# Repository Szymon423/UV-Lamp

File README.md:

<div align="center">

# 💅 UV Lamp Project

*A custom-made UV lamp for nail polish curing*

</div>

---

## 📖 About

In this project, I wanted to address a common issue in the beauty industry: **misleading UV lamp specifications**. 

Most commercial UV lamps are advertised as "60W UV lamps" while being supplied with only 15W power adapters. I wanted to create something honest and effective, so I designed this lamp from scratch.

### ✨ Key Features

- **True 45W electrical power** - honest specifications
- **Adjustable power settings** - customize intensity from 0-100%
- **Configurable timer** - set precise curing times up to 3 minutes
- **Intuitive touchscreen interface** - easy configuration with rotary encoder
- **Settings persistence** - preferences saved in flash memory
- **Professional UV wavelength** - 395-405nm LEDs for optimal curing

<div align="center">

### 🎨 Main Design

### 🖼️ Detailed Views

<table>
  <tr>
    <td width="50%">
      
    </td>
    <td width="50%">
      
    </td>
  </tr>
  <tr>
    <td width="50%">
      
    </td>
    <td width="50%">
      
    </td>
  </tr>
  <tr>
    <td width="50%">
      
    </td>
    <td width="50%">
      
    </td>
  </tr>
  <tr>
    <td width="50%">
      
    </td>
    <td cwidth="50%">
      
    </td>
  </tr>
</table>

</div>

---

## ⚡ Hardware Design

The hardware was designed in **KiCad** around the **Raspberry Pi RP2040** microcontroller. The lamp is powered through a C8 socket connector from 230V AC mains.

### 🔧 PCB Architecture

The system consists of three types of PCBs:

1. **Power & Driver Board**
   - Converts 230V AC to 48V DC for LED drivers
   - Provides 3.3V DC for microcontroller and peripherals
   - LED current drivers with PWM control capability

2. **Control Board**
   - RP2040 microcontroller
   - 1.69" LCD display with LVGL interface
   - Rotary encoder for navigation
   - Two control buttons
   - Flash memory for settings storage

3. **LED Arrays**
   - Multiple LED strings with 395-405nm wavelength
   - Optimized thermal management
   - Uniform light distribution

### 📊 Technical Specifications

- **Input voltage:** 230V AC (50/60Hz)
- **LED power:** 48V DC, up to 45W total
- **UV wavelength:** 395-405nm
- **Control:** PWM dimming, 0-100%
- **Timer range:** 0-180 seconds
- **Display:** 1.69" color LCD (280x240)

---

## 💻 Software

The firmware is written in C for the RP2040 and utilizes the following technologies:

### 🛠️ Core Technologies

- **LVGL (Light and Versatile Graphics Library)** - for the graphical interface
- **SquareLine Studio** - for UI design
- **Pico SDK** - official Raspberry Pi development kit
- **Hardware PWM** - for precise LED dimming control

### 🖥️ User Interface

<div align="center">

</div>

The interface features three main screens:

1. **Main Screen** - displays current timer and power settings with arc progress indicator
2. **Power Configuration** - adjust UV intensity from 0-100%
3. **Timer Configuration** - set curing time from 0 to 180 seconds

### 🎮 Controls

- **Rotary Encoder** - navigate and adjust values
- **Button 1** - short press: change screen | long press: enter/exit edit mode
- **Button 2** - short press: start/pause timer | long press: reset timer

### 🚀 Features

- Smooth animations and transitions
- Real-time countdown with arc visualization
- Automatic settings save to flash memory
- Debounced button inputs with long-press detection
- 30 FPS refresh rate for fluid UI

---

## 📜 License

This project is open source. Feel free to use, modify, and distribute according to the license terms.

---

## 🙏 Acknowledgments

This project was created because my girlfriend complained about her unreliable UV lamp. It combines my passion for electronics and design with practical problem-solving.

---

<div align="center">

*Made with dedication to quality and honesty*

</div>

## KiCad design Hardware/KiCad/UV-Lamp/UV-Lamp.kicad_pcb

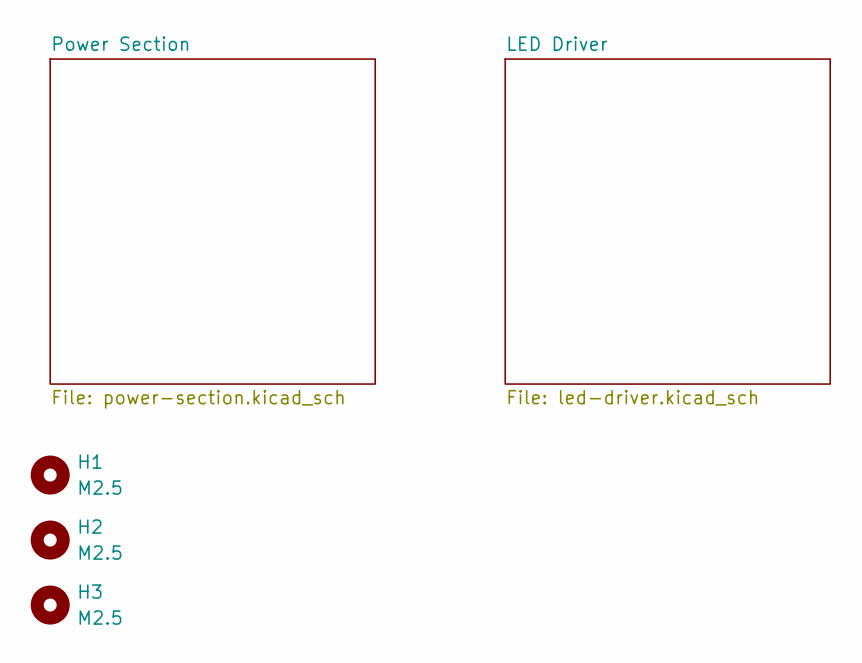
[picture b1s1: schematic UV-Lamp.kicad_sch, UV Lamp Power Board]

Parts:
H1, H2, H3: M2.5; MountingHole_2.7mm_M2.5

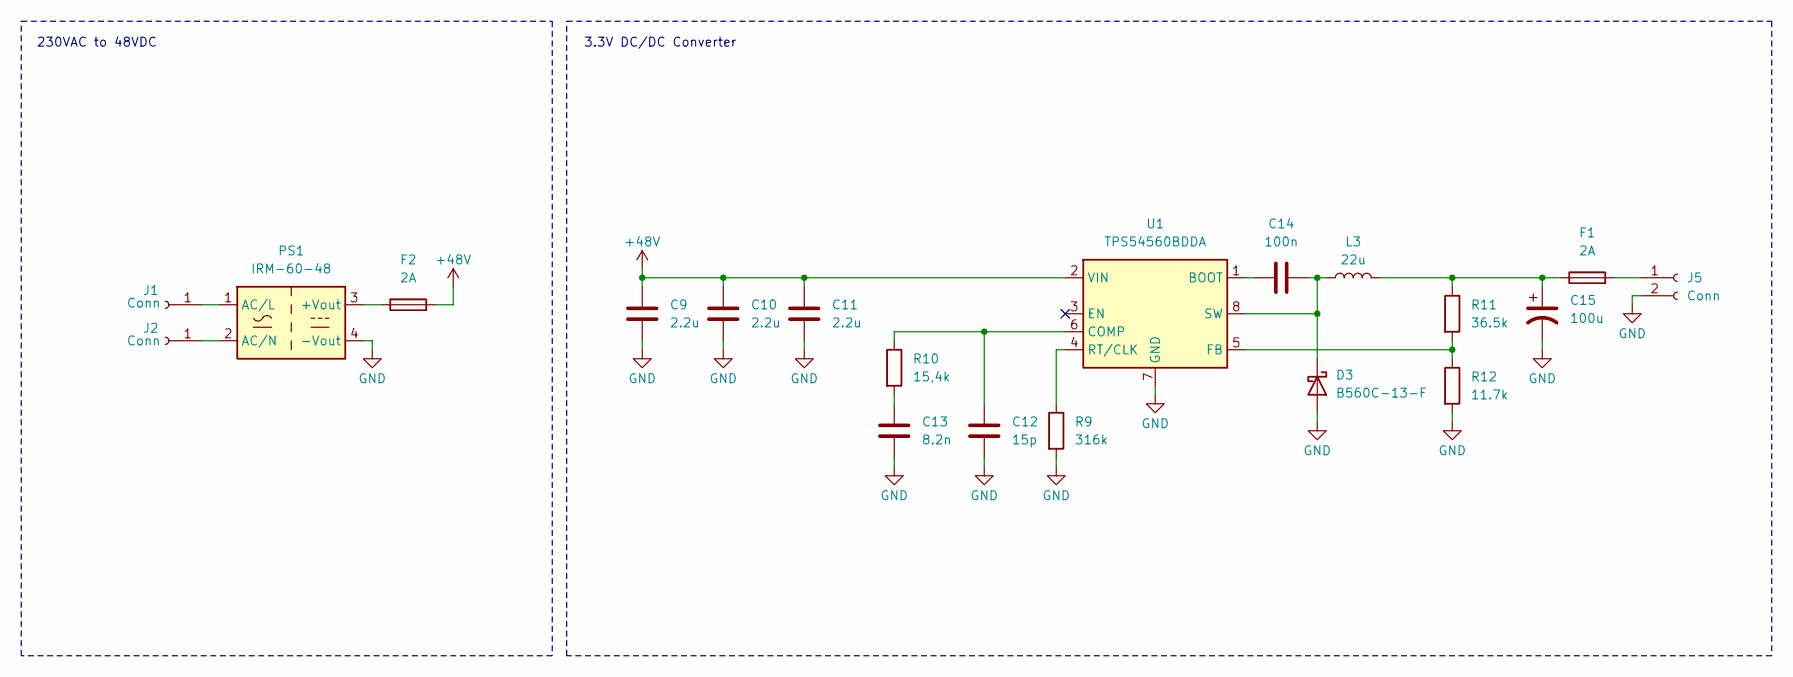
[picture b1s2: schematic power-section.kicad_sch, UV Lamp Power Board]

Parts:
C9, C10, C11: 2.2u; C_1206_3216Metric
C12: 15p; C_0805_2012Metric
C13: 8.2n; C_0805_2012Metric
C14: 100n; C_0805_2012Metric
C15: 100u; CP_Elec_6.3x7.7
D3: B560C-13-F; D_SMC
F1, F2: 2A; Fuse_1206_3216Metric
J1, J2: Conn; SolderWire-1.5sqmm_1x01_D1.7mm_OD3.9mm
J5: Conn; SolderWire-1sqmm_1x02_P5.4mm_D1.4mm_OD2.7mm
L3: 22u; L_12x12mm_H6mm
PS1: IRM-60-48; Converter_ACDC_MeanWell_IRM-60-xx_THT
R9: 316k; R_0805_2012Metric
R10: 15,4k; R_0805_2012Metric
R11: 36.5k; R_0805_2012Metric
R12: 11.7k; R_0805_2012Metric
U1: TPS54560BDDA; Texas_R-PDSO-G8_EP2.95x4.9mm_Mask2.4x3.1mm_ThermalVias

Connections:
+48V: C9.1, C10.1, C11.1, F2.2, U1.2 (VIN); also elsewhere on the board
GND: C9.2, C10.2, C11.2, C12.2, C13.2, C15.2, D3.2 (A), J5.2, PS1.4 (-Vout), R9.2, R12.2, U1.7 (GND), U1.9 (GND); also elsewhere on the board
unnamed: C13.1, R10.2
unnamed: C15.1, F1.1, L3.2, R11.1
unnamed: C14.2, D3.1 (K), L3.1, U1.8 (SW)
unnamed: J1.1, PS1.1 (AC/L)
unnamed: J2.1, PS1.2 (AC/N)
unnamed: F1.2, J5.1
unnamed: F2.1, PS1.3 (+Vout)
unnamed: C14.1, U1.1 (BOOT)
unnamed: C12.1, R10.1, U1.6 (COMP)
unnamed: R11.2, R12.1, U1.5 (FB)
unnamed: R9.1, U1.4 (RT/CLK)

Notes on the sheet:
230VAC to 48VDC
3.3V DC/DC Converter

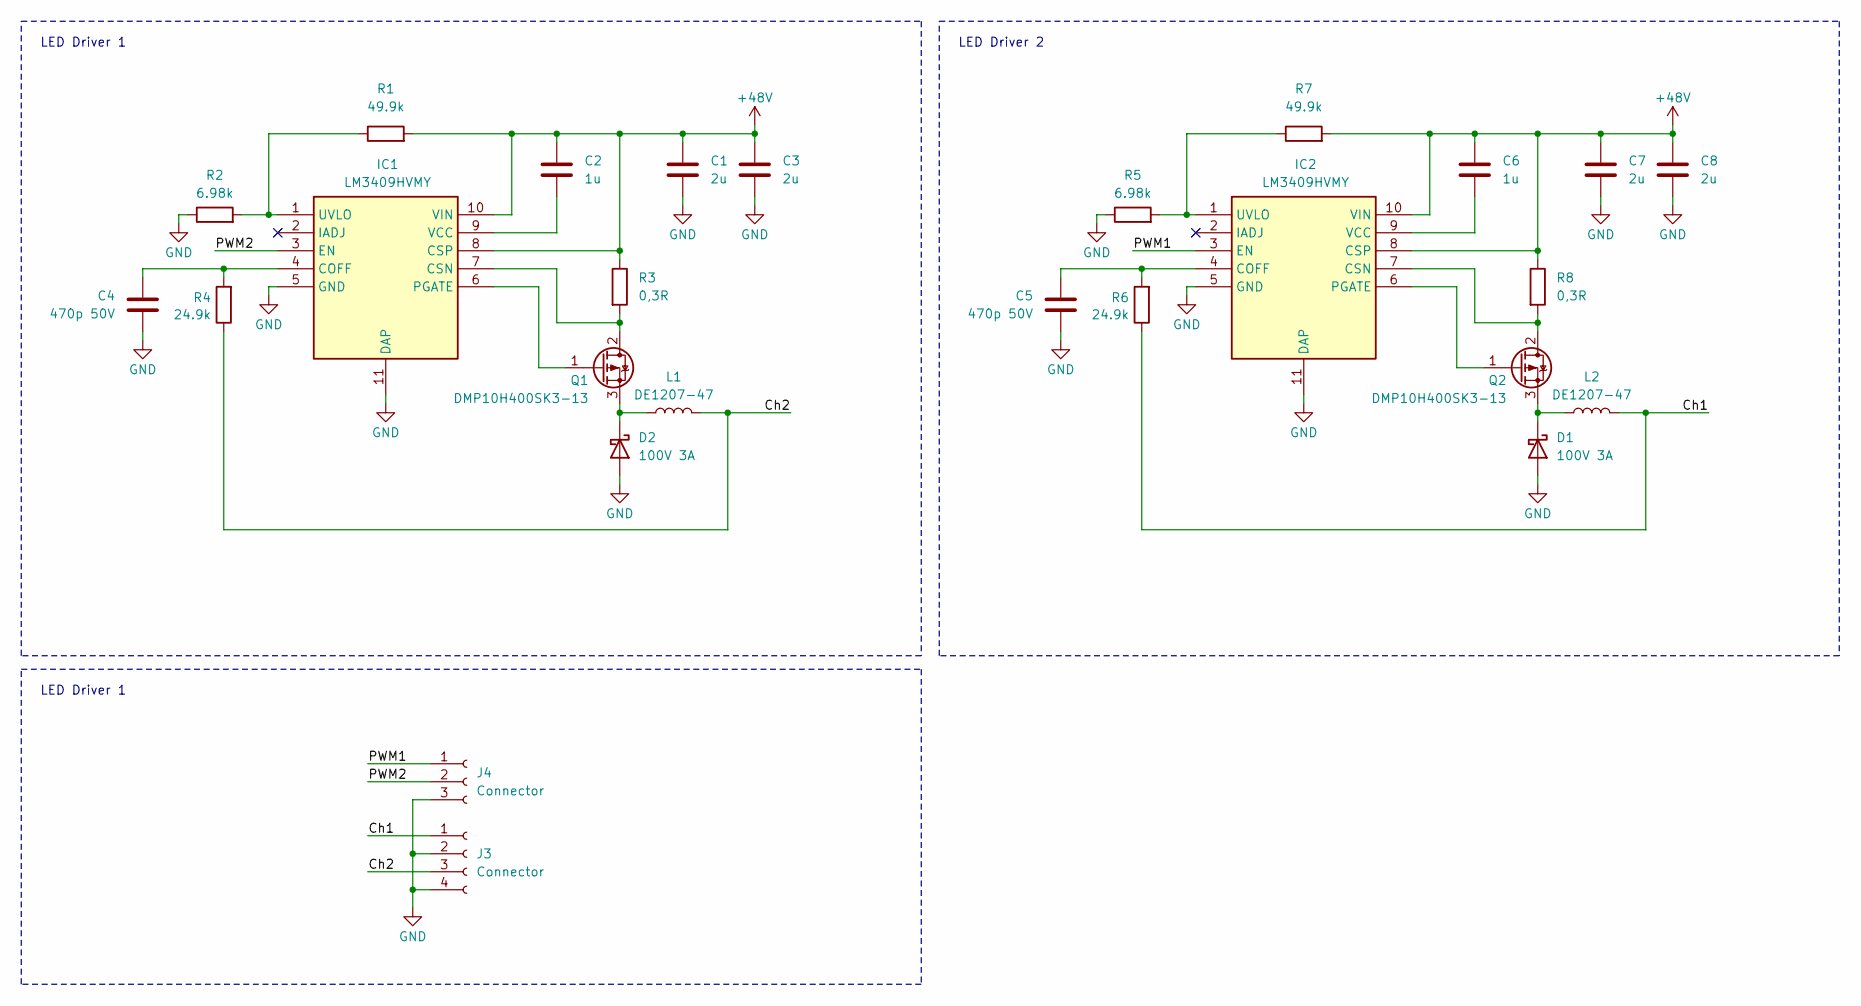
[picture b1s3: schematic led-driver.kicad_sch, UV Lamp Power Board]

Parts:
C1, C3, C7, C8: 2u; C_1206_3216Metric
C2, C6: 1u; C_0805_2012Metric
C4, C5: 470p 50V; C_0805_2012Metric
D1, D2: 100V 3A; D_SMC
IC1, IC2: LM3409HVMY; Manufacturer_Part_Number LM3409HVMY/NOPB
J3: Connector; SolderWire-1.5sqmm_1x04_P6mm_D1.7mm_OD3mm
J4: Connector; SolderWire-0.5sqmm_1x03_P4.6mm_D0.9mm_OD2.1mm
L1, L2: DE1207-47; L_12x12mm_H6mm
Q1, Q2: DMP10H400SK3-13; TO-252-2
R1, R7: 49.9k; R_0805_2012Metric
R2, R5: 6.98k; R_0805_2012Metric
R3, R8: 0,3R; R_2512_6332Metric
R4, R6: 24.9k; R_0805_2012Metric

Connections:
+48V: C1.1, C2.1, C3.1, C6.1, C7.1, C8.1, IC1.8 (CSP), IC1.10 (VIN), IC2.8 (CSP), IC2.10 (VIN), R1.2, R3.1, R7.2, R8.1; also elsewhere on the board
/LED Driver/Ch1: J3.1, L2.2, R6.1
/LED Driver/Ch2: J3.3, L1.2, R4.1
/LED Driver/PWM1: IC2.3 (EN), J4.1
/LED Driver/PWM2: IC1.3 (EN), J4.2
GND: C1.2, C3.2, C4.2, C5.2, C7.2, C8.2, D1.2 (A), D2.2 (A), IC1.5 (GND), IC1.11 (DAP), IC2.5 (GND), IC2.11 (DAP), J3.2, J3.4, J4.3, R2.1, R5.1; also elsewhere on the board
unnamed: D1.1 (K), L2.1, Q2.3 (S)
unnamed: D2.1 (K), L1.1, Q1.3 (S)
unnamed: C4.1, IC1.4 (COFF), R4.2
unnamed: IC1.7 (CSN), Q1.2 (D), R3.2
unnamed: IC1.6 (PGATE), Q1.1 (G)
unnamed: IC1.1 (UVLO), R1.1, R2.2
unnamed: C2.2, IC1.9 (VCC)
unnamed: C5.1, IC2.4 (COFF), R6.2
unnamed: IC2.7 (CSN), Q2.2 (D), R8.2
unnamed: IC2.6 (PGATE), Q2.1 (G)
unnamed: IC2.1 (UVLO), R5.2, R7.1
unnamed: C6.2, IC2.9 (VCC)

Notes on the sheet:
LED Driver 2
LED Driver 1

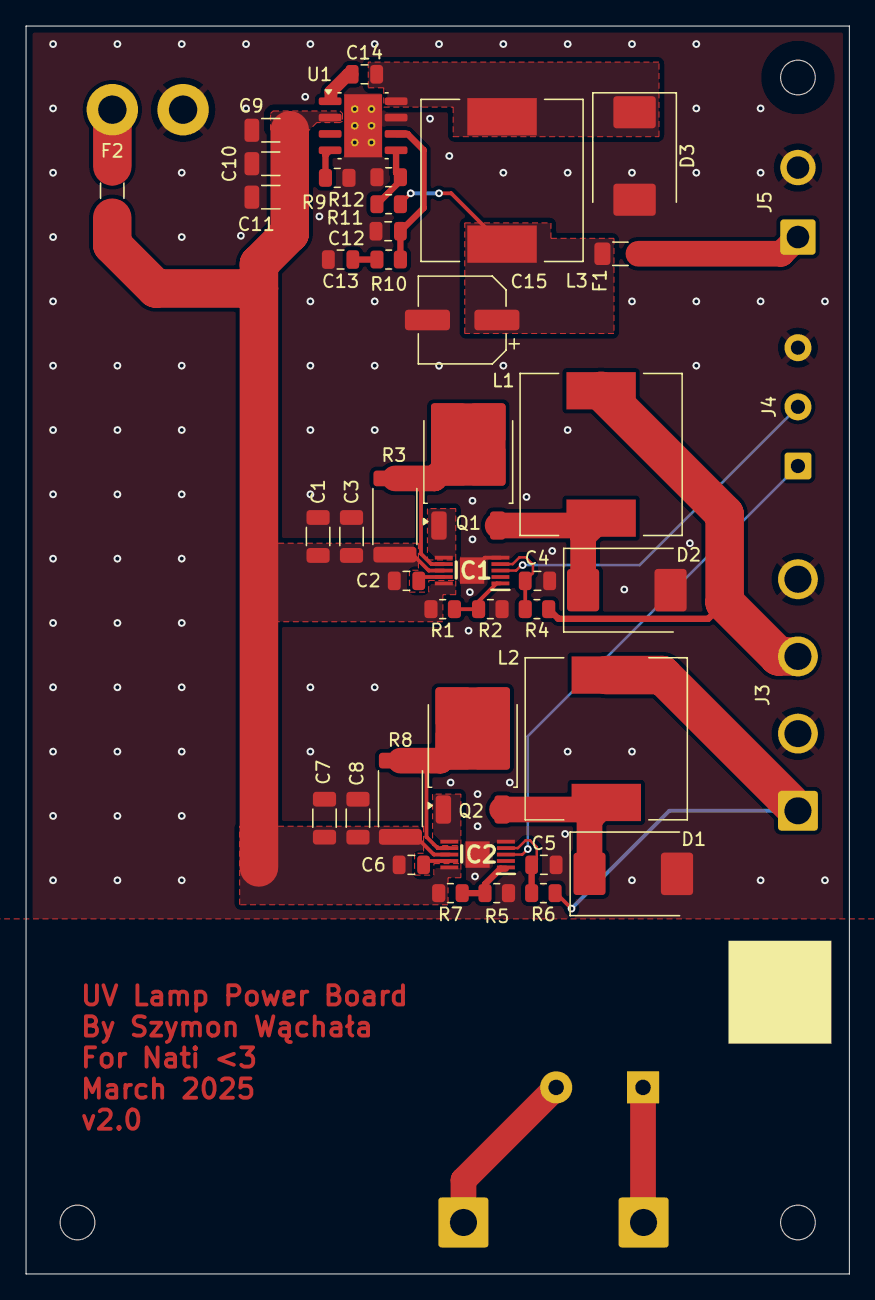
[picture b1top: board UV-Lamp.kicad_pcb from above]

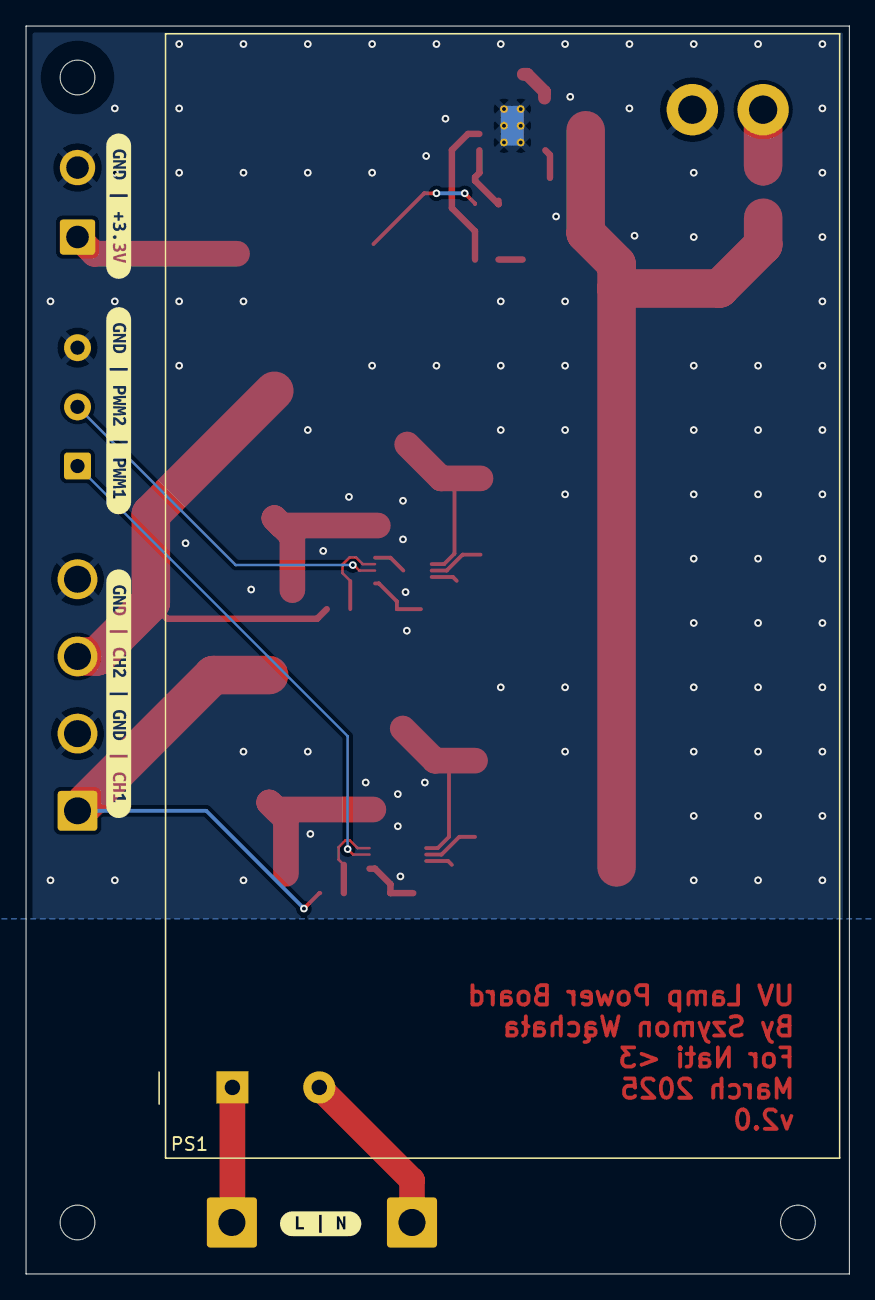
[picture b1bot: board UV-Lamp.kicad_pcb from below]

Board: 2 copper layers, 64.0 x 97.0 mm, 53 parts (5 on the bottom side), 29 nets.

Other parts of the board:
kibuzzard-67E995BA: G***; kibuzzard-67E995BA
kibuzzard-67E9956E: G***; kibuzzard-67E9956E
kibuzzard-67E99536: G***; kibuzzard-67E99536
kibuzzard-67E99669: G***; kibuzzard-67E99669

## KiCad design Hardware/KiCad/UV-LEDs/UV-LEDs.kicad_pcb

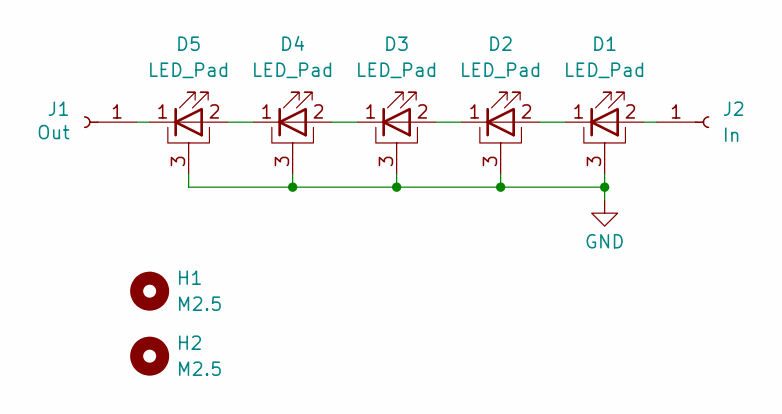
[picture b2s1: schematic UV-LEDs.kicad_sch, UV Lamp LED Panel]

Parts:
D1, D2, D3, D4, D5: LED_Pad; LED_Cree-XHP35
H1, H2: M2.5; MountingHole_2.7mm_M2.5
J1: Out; SolderWire-1.5sqmm_1x01_D1.7mm_OD3.9mm
J2: In; SolderWire-1.5sqmm_1x01_D1.7mm_OD3.9mm

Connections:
GND: D1.3 (PAD), D2.3 (PAD), D3.3 (PAD), D4.3 (PAD), D5.3 (PAD)
unnamed: D1.2 (A), J2.1
unnamed: D1.1 (K), D2.2 (A)
unnamed: D2.1 (K), D3.2 (A)
unnamed: D3.1 (K), D4.2 (A)
unnamed: D4.1 (K), D5.2 (A)
unnamed: D5.1 (K), J1.1

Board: 2 copper layers, 11 parts (0 on the bottom side), 7 nets, no tracks yet.

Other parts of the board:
kibuzzard-67E9A14C: G***; kibuzzard-67E9A14C
kibuzzard-67E9A164: G***; kibuzzard-67E9A164

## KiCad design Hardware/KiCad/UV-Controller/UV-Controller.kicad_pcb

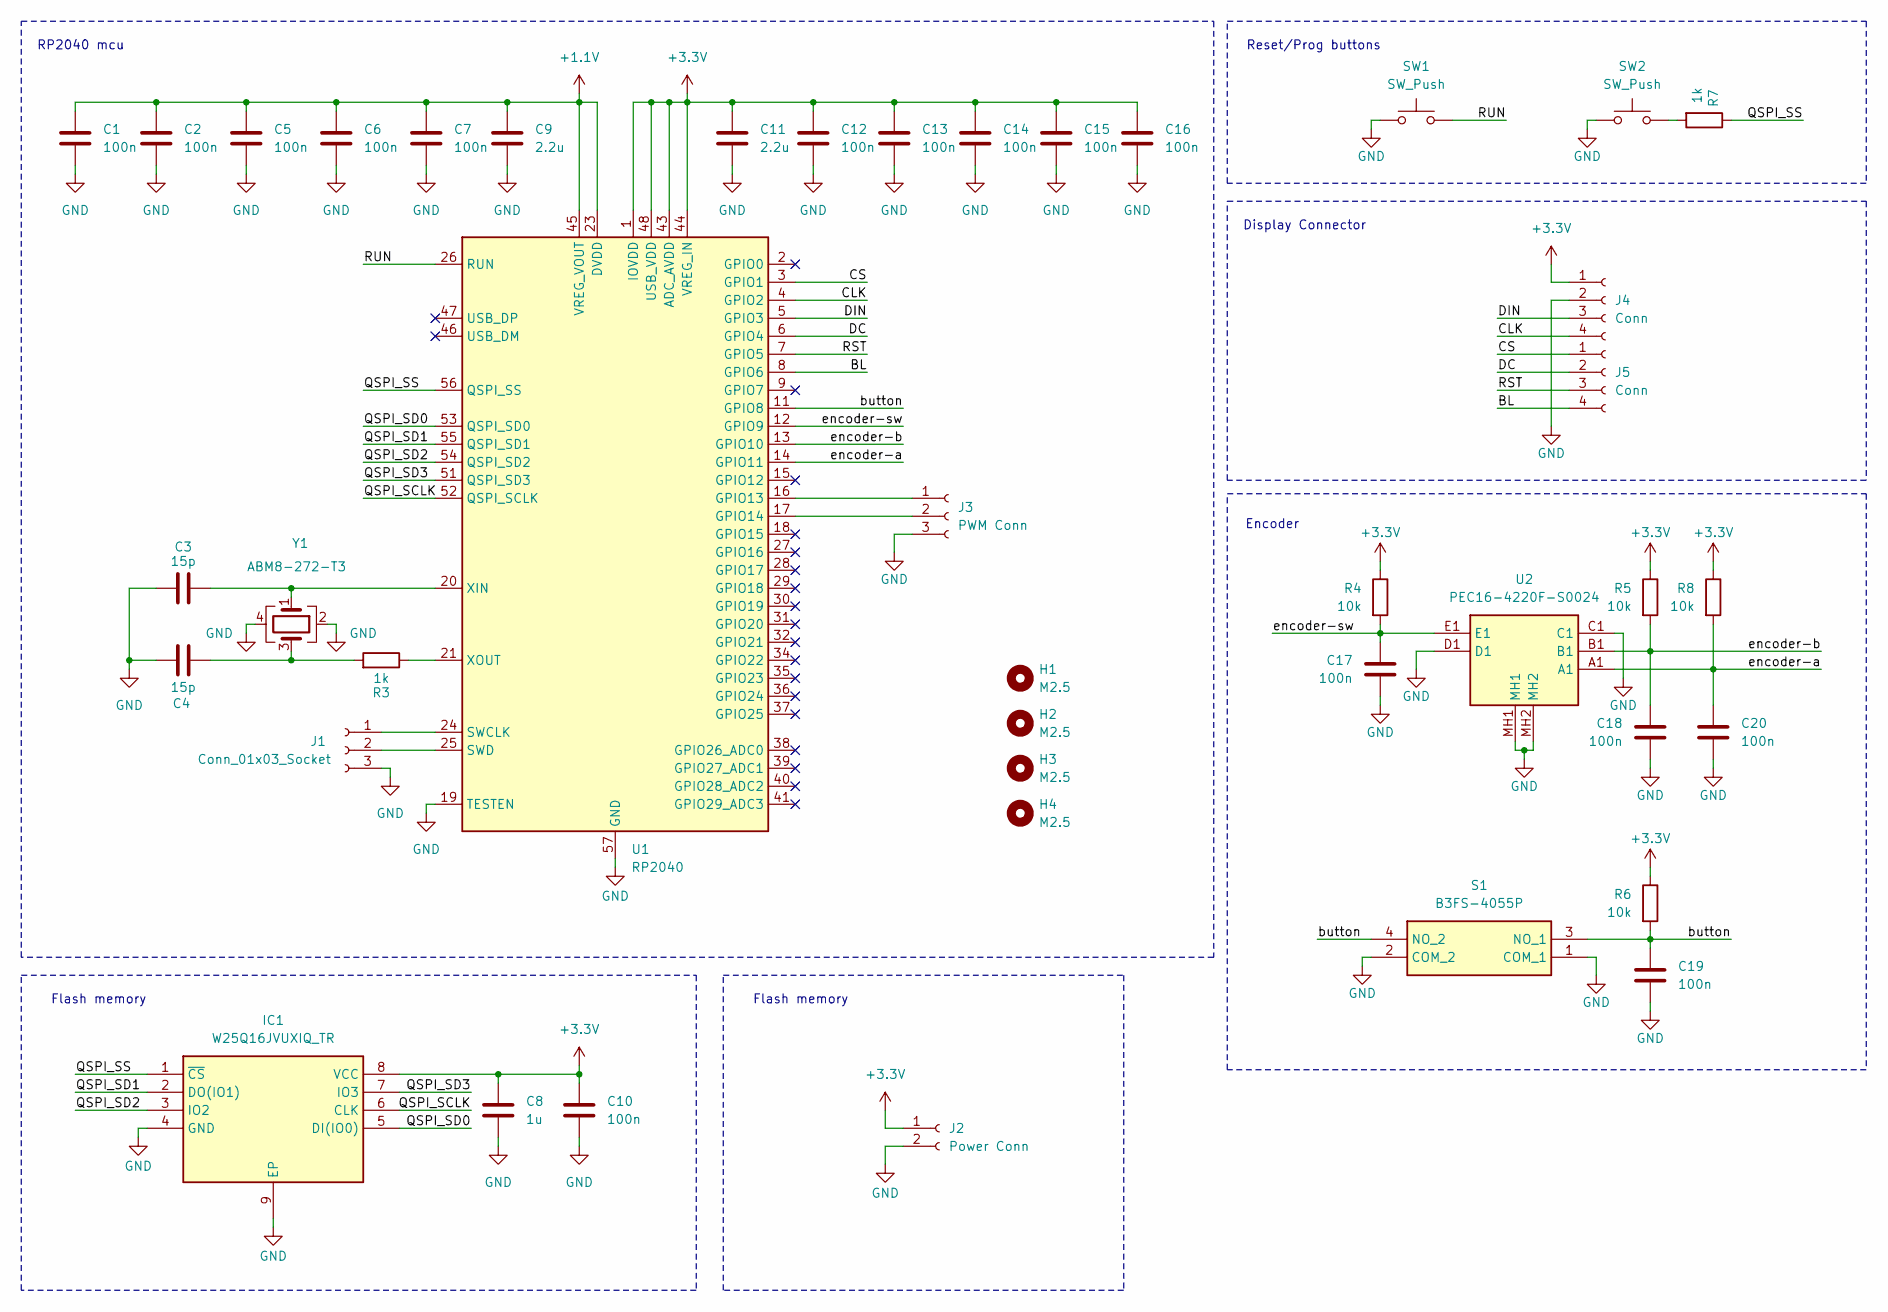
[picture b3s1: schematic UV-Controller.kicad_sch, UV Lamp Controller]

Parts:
C1, C2, C5, C6, C7, C10, C12, C13, C14, C15, C16: 100n; C_0402_1005Metric
C3, C4: 15p; C_0402_1005Metric
C8: 1u; C_0805_2012Metric
C9, C11: 2.2u; C_0805_2012Metric
C17, C18, C19, C20: 100n; C_0805_2012Metric
H1, H2, H3, H4: M2.5; MountingHole_2.7mm_M2.5
IC1: W25Q16JVUXIQ_TR; SON50P300X200X60-9N; Manufacturer_Part_Number W25Q16JVUXIQ TR
J1: Conn_01x03_Socket; JST_PH_S3B-PH-K_1x03_P2.00mm_Horizontal
J2: Power Conn; SolderWire-1.5sqmm_1x02_P6mm_D1.7mm_OD3mm
J3: PWM Conn; SolderWire-0.5sqmm_1x03_P4.6mm_D0.9mm_OD2.1mm
J4, J5: Conn; SolderWire-0.5sqmm_1x04_P4.6mm_D0.9mm_OD2.1mm
R3, R7: 1k; R_0402_1005Metric
R4, R5, R6, R8: 10k; R_0805_2012Metric
S1: B3FS-4055P; Manufacturer_Part_Number B3FS-4055P
SW1, SW2: SW_Push; SW_Tactile_SPST_NO_Straight_CK_PTS636Sx25SMTRLFS
U1: RP2040; QFN-56-1EP_7x7mm_P0.4mm_EP3.2x3.2mm_ThermalVias
U2: PEC16-4220F-S0024; Manufacturer_Part_Number PEC16-4220F-S0024
Y1: ABM8-272-T3; Crystal_SMD_Abracon_ABM3B-4Pin_5.0x3.2mm

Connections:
+1.1V: C1.1, C2.1, C5.1, C6.1, C7.1, C9.1, U1.23 (DVDD), U1.45 (VREG_VOUT), U1.50 (DVDD)
+3.3V: C8.1, C10.1, C11.1, C12.1, C13.1, C14.1, C15.1, C16.1, IC1.8 (VCC), J2.1, J4.1, R4.1, R5.1, R6.1, R8.1, U1.1 (IOVDD), U1.10 (IOVDD), U1.22 (IOVDD), U1.33 (IOVDD), U1.42 (IOVDD), U1.43 (ADC_AVDD), U1.44 (VREG_IN), U1.48 (USB_VDD), U1.49 (IOVDD)
/BL: J5.4, U1.8 (GPIO6)
/CLK: J4.4, U1.4 (GPIO2)
/CS: J5.1, U1.3 (GPIO1)
/DC: J5.2, U1.6 (GPIO4)
/DIN: J4.3, U1.5 (GPIO3)
/QSPI_SCLK: IC1.6 (CLK), U1.52 (QSPI_SCLK)
/QSPI_SD0: IC1.5 (DI(IO0)), U1.53 (QSPI_SD0)
/QSPI_SD1: IC1.2 (DO(IO1)), U1.55 (QSPI_SD1)
/QSPI_SD2: IC1.3 (IO2), U1.54 (QSPI_SD2)
/QSPI_SD3: IC1.7 (IO3), U1.51 (QSPI_SD3)
/QSPI_SS: IC1.1 (~CS), R7.1, U1.56 (QSPI_SS)
/RST: J5.3, U1.7 (GPIO5)
/RUN: SW1.2, U1.26 (RUN)
/button: C19.1, R6.2, S1.3 (NO_1), S1.4 (NO_2), U1.11 (GPIO8)
/encoder-a: C20.1, R8.2, U1.14 (GPIO11), U2.A1
/encoder-b: C18.1, R5.2, U1.13 (GPIO10), U2.B1
/encoder-sw: C17.1, R4.2, U1.12 (GPIO9), U2.E1
GND: C1.2, C2.2, C3.1, C4.1, C5.2, C6.2, C7.2, C8.2, C9.2, C10.2, C11.2, C12.2, C13.2, C14.2, C15.2, C16.2, C17.2, C18.2, C19.2, C20.2, IC1.4 (GND), IC1.9 (EP), J1.3, J2.2, J3.3, J4.2, S1.1 (COM_1), S1.2 (COM_2), SW1.1, SW2.1, U1.19 (TESTEN), U1.57 (GND), U2.C1, U2.D1, U2.MH1, U2.MH2, Y1.2, Y1.4
unnamed: C4.2, R3.2, Y1.3
unnamed: J1.1, U1.24 (SWCLK)
unnamed: J1.2, U1.25 (SWD)
unnamed: J3.1, U1.16 (GPIO13)
unnamed: J3.2, U1.17 (GPIO14)
unnamed: R7.2, SW2.2
unnamed: C3.2, U1.20 (XIN), Y1.1
unnamed: R3.1, U1.21 (XOUT)

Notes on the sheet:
Encoder
Display Connector
Flash memory
RP2040 mcu
Reset/Prog buttons

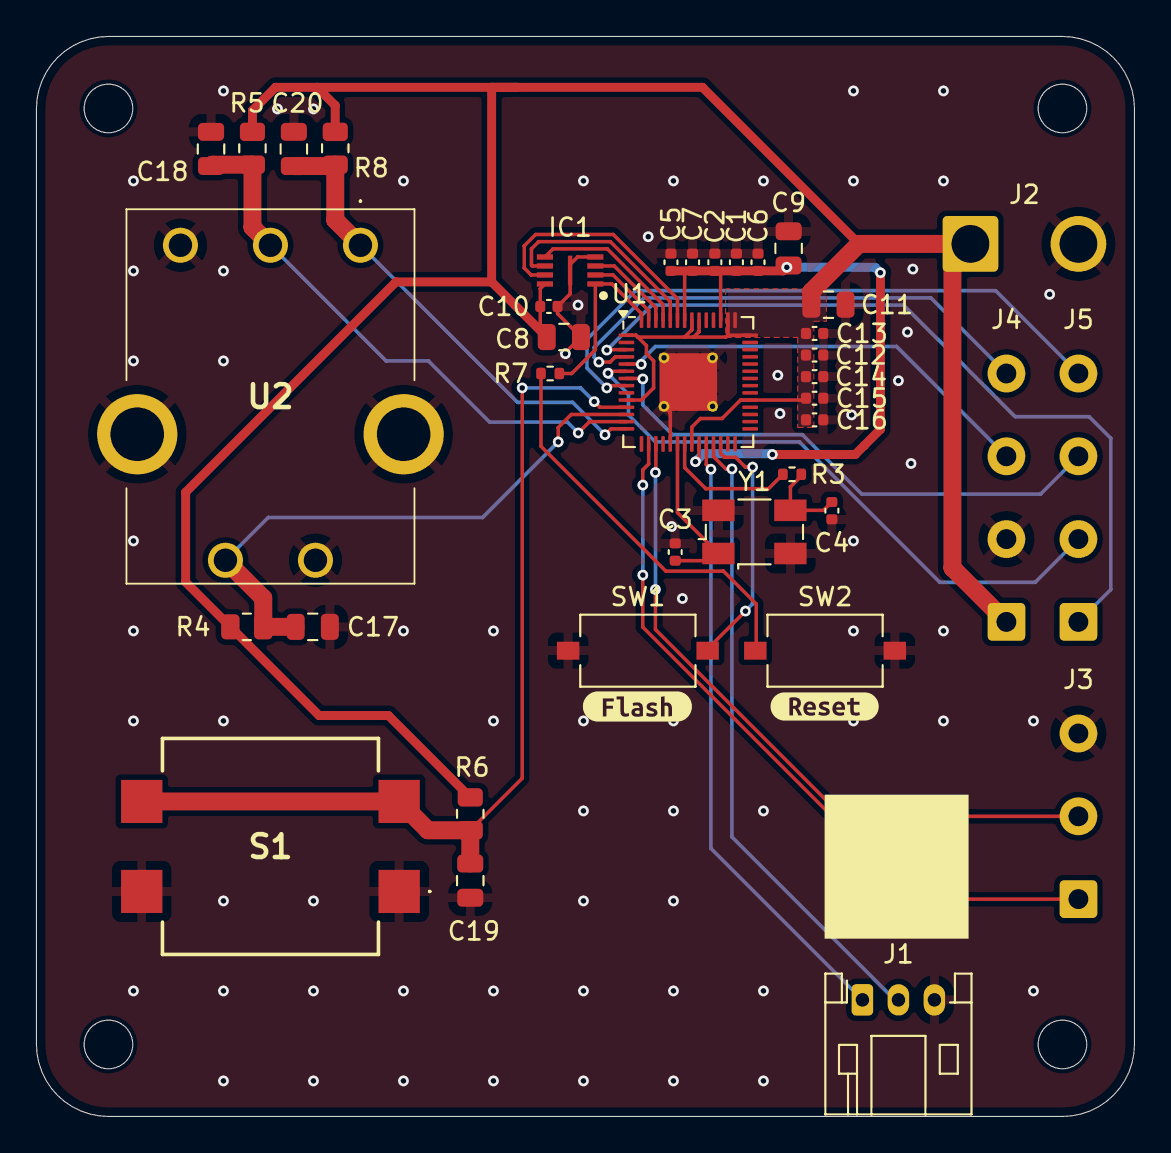
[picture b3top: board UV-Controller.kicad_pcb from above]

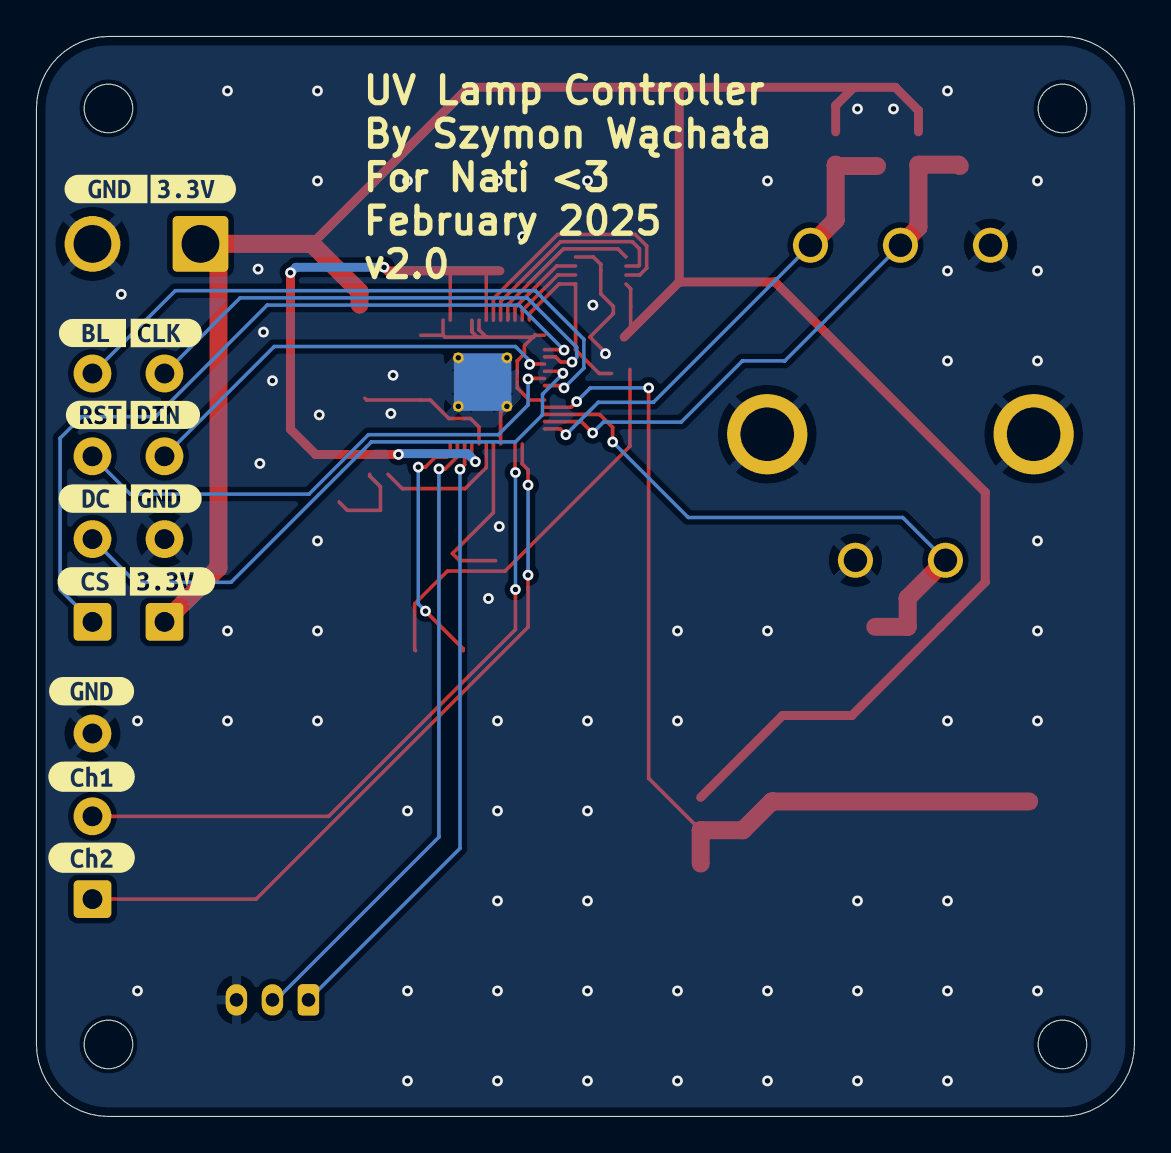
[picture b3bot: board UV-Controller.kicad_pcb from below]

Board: 2 copper layers, 61.0 x 60.0 mm, 57 parts (13 on the bottom side), 28 nets.

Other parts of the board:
kibuzzard-67EEDD31: G***; kibuzzard-67EEDD31
kibuzzard-67EEDD44: G***; kibuzzard-67EEDD44
kibuzzard-67EEDF74: G***; kibuzzard-67EEDF74
kibuzzard-67EEDFA4: G***; kibuzzard-67EEDFA4
kibuzzard-67EEDFD5: G***; kibuzzard-67EEDFD5
kibuzzard-67EEDFDD, kibuzzard-67EEDFDD#2: G***; kibuzzard-67EEDFDD
kibuzzard-67EEDFE5: G***; kibuzzard-67EEDFE5
kibuzzard-67EEDFEA: G***; kibuzzard-67EEDFEA
kibuzzard-67EEE00C: G***; kibuzzard-67EEE00C
kibuzzard-67EEE0EE: G***; kibuzzard-67EEE0EE
kibuzzard-67EEE001: G***; kibuzzard-67EEE001
kibuzzard-67EEE14D: G***; kibuzzard-67EEE14D
kibuzzard-67EEE147: G***; kibuzzard-67EEE147
kibuzzard-67EEE153: G***; kibuzzard-67EEE153

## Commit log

2025-04-02 Designed simple enclosure
2025-04-03 Prepared gerbers for prod
2025-04-03 Initialized software project
2025-04-03 Started writing graphics library for display
2025-10-16 Updating what's left on windows
2025-10-16 Added list of components
2025-10-31 Big update
2025-10-31 please work
2025-10-31 Added renders with cool readme
2025-10-31 One more fix
